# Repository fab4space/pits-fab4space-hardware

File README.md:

# pits-fab4space-hardware
pits-fab4space-hardware

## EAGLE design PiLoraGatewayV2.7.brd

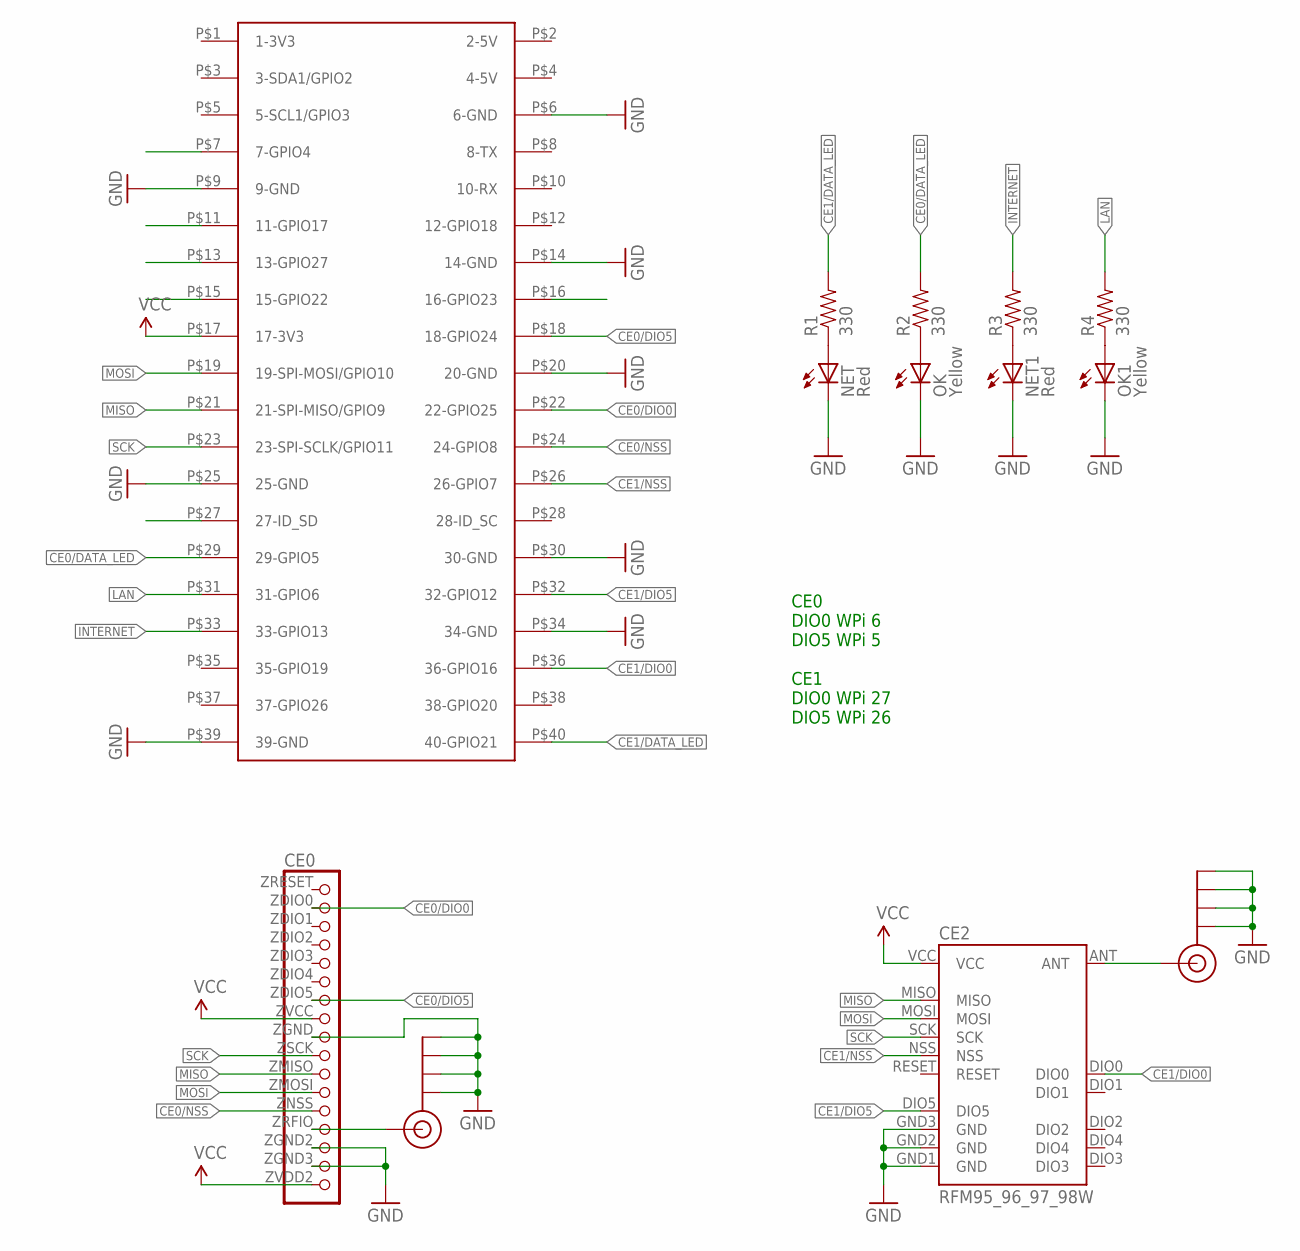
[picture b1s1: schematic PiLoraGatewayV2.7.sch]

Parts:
CE0: DRF1278F_BKOUTDP1276; ANYLINK_DP1276
CE2: RFM95_96_97_98W
J$1, J$2: SMA_EDGE; SMA-EDGE
NET, NET1: Red; LED-0603
OK, OK1: Yellow; LED-0603
R1, R2, R3, R4: 330; 0603-RES
U$1: RASPBERRY-PI+; RASPBERRY-PI-PLUS-CAM_NOTCH

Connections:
CE0/DATA_LED: R2.2, U$1.P$29 (29-GPIO5)
CE0/DIO0: CE0.ZDIO0 (DIO0), U$1.P$22 (22-GPIO25)
CE0/DIO5: CE0.ZDIO5 (DIO5), U$1.P$18 (18-GPIO24)
CE0/NSS: CE0.ZNSS (NSS), U$1.P$24 (24-GPIO8)
CE1/DATA_LED: R1.2, U$1.P$40 (40-GPIO21)
CE1/DIO0: CE2.DIO0, U$1.P$36 (36-GPIO16)
CE1/DIO5: CE2.DIO5, U$1.P$32 (32-GPIO12)
CE1/NSS: CE2.NSS, U$1.P$26 (26-GPIO7)
GND: CE0.ZGND (GND), CE0.ZGND2 (RGND1), CE0.ZGND3 (RGND2), CE2.GND1 (GND), CE2.GND2 (GND), CE2.GND3 (GND), J$1.GND@0 (GND), J$1.GND@1 (GND), J$1.GND@2 (GND), J$1.GND@3 (GND), J$2.GND@0 (GND), J$2.GND@1 (GND), J$2.GND@2 (GND), J$2.GND@3 (GND), NET.C, NET1.C, OK.C, OK1.C, U$1.P$6 (6-GND), U$1.P$9 (9-GND), U$1.P$14 (14-GND), U$1.P$20 (20-GND), U$1.P$25 (25-GND), U$1.P$30 (30-GND), U$1.P$34 (34-GND), U$1.P$39 (39-GND)
INTERNET: R3.2, U$1.P$33 (33-GPIO13)
LAN: R4.2, U$1.P$31 (31-GPIO6)
MISO: CE0.ZMISO (MISO), CE2.MISO, U$1.P$21 (21-SPI-MISO/GPIO9)
MOSI: CE0.ZMOSI (MOSI), CE2.MOSI, U$1.P$19 (19-SPI-MOSI/GPIO10)
unnamed: CE0.ZRFIO (RFIO), J$1.SIG (SIGNAL)
unnamed: NET1.A, R3.1
unnamed: OK1.A, R4.1
unnamed: OK.A, R2.1
unnamed: NET.A, R1.1
S$1: CE2.ANT, J$2.SIG (SIGNAL)
SCK: CE0.ZSCK (SCK), CE2.SCK, U$1.P$23 (23-SPI-SCLK/GPIO11)
VCC: CE0.ZVCC (VCC), CE0.ZVDD2 (VCC2), CE2.VCC, U$1.P$17 (17-3V3)

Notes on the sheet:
CE0 DIO0 WPi 6 DIO5 WPi 5 CE1 DIO0 WPi 27 DIO5 WPi 26

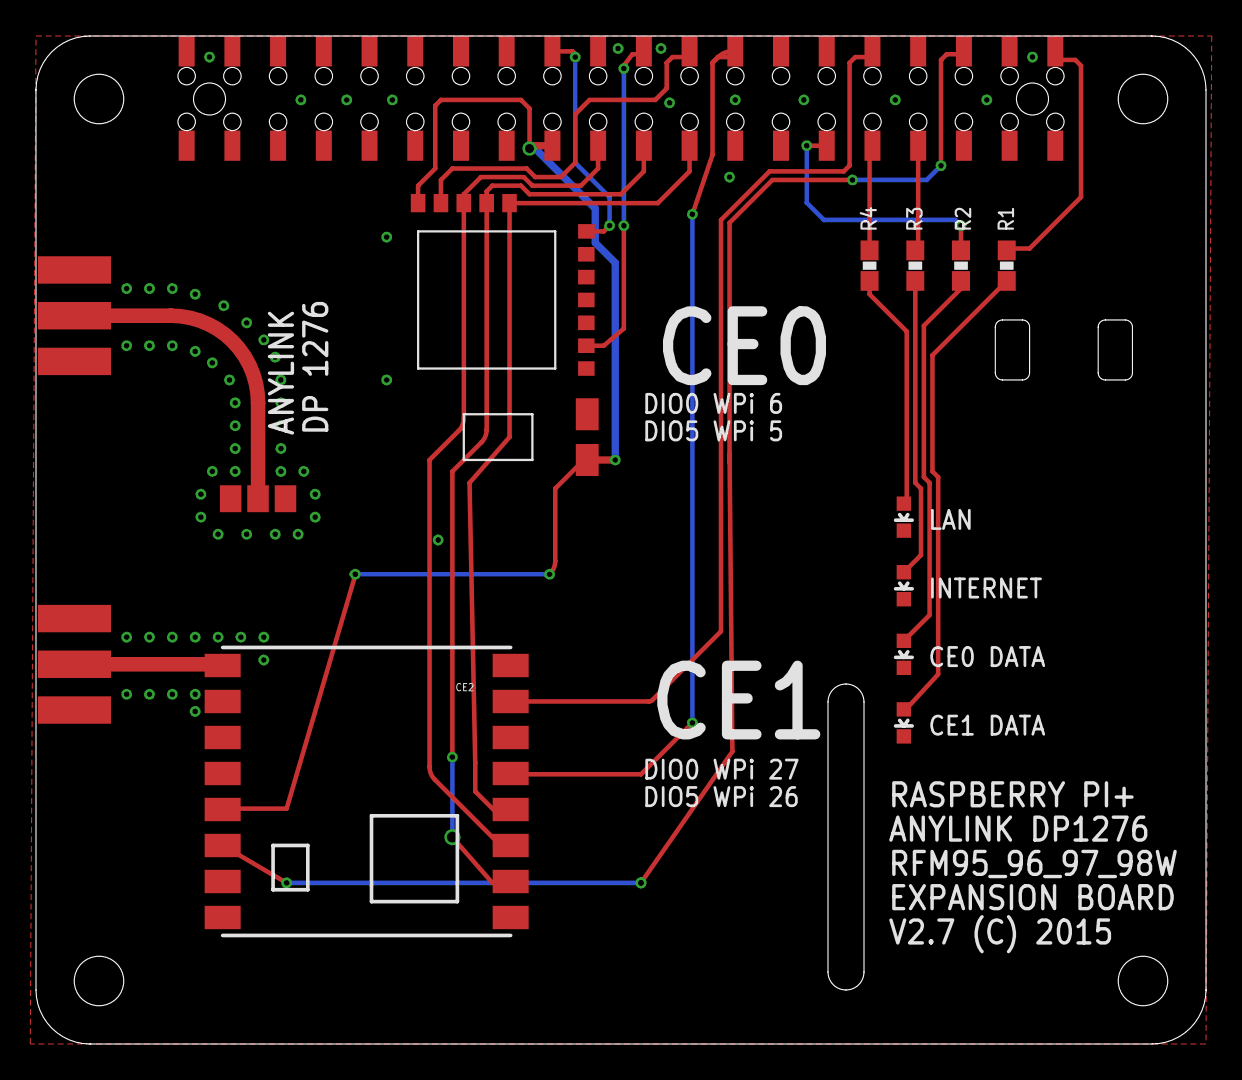
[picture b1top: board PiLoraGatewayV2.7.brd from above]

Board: 2 copper layers, 65.0 x 56.0 mm, 13 parts (0 on the bottom side), 21 nets.

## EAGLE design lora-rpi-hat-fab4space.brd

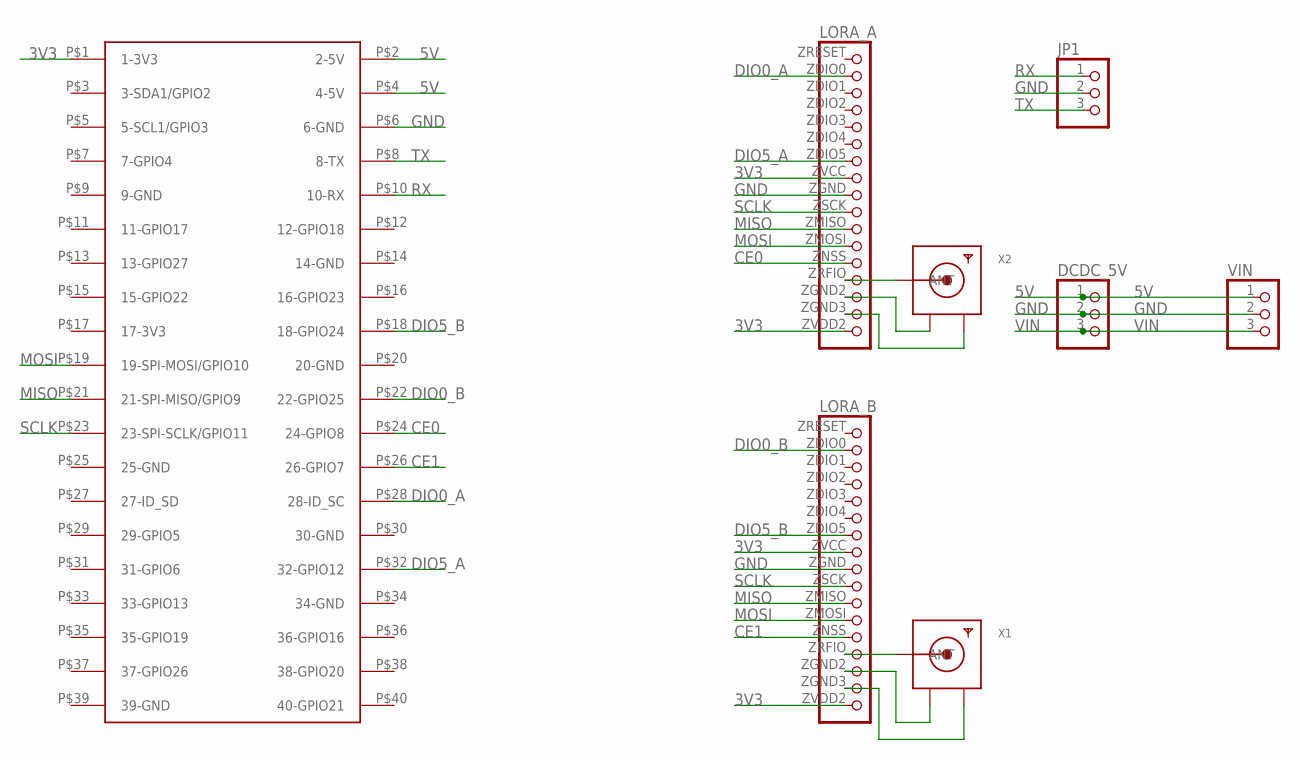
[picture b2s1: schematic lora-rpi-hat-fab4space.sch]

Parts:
DCDC_5V: PINHD-1X3; 1X03
JP1: PINHD-1X3; 1X03
LORA_A: DRF1278F_BKOUTDP1276; ANYLINK_DP1276
LORA_B: DRF1278F_BKOUTDP1276; ANYLINK_DP1276
U$1: RASPBERRY-PI+; RASPBERRY-PI-PLUS-CAM_NOTCH
VIN: PINHD-1X3; 1X03
X1, X2: SMACONNECTOR_EDGE; SMA_EDGELAUNCH

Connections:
3V3: LORA_A.ZVCC (VCC), LORA_A.ZVDD2 (VCC2), LORA_B.ZVCC (VCC), LORA_B.ZVDD2 (VCC2), U$1.P$1 (1-3V3)
5V: DCDC_5V.1, U$1.P$2 (2-5V), U$1.P$4 (4-5V), VIN.1
CE0: LORA_A.ZNSS (NSS), U$1.P$24 (24-GPIO8)
CE1: LORA_B.ZNSS (NSS), U$1.P$26 (26-GPIO7)
DIO0_A: LORA_A.ZDIO0 (DIO0), U$1.P$28 (28-ID_SC)
DIO0_B: LORA_B.ZDIO0 (DIO0), U$1.P$22 (22-GPIO25)
DIO5_A: LORA_A.ZDIO5 (DIO5), U$1.P$32 (32-GPIO12)
DIO5_B: LORA_B.ZDIO5 (DIO5), U$1.P$18 (18-GPIO24)
GND: DCDC_5V.2, JP1.2, LORA_A.ZGND (GND), LORA_B.ZGND (GND), U$1.P$6 (6-GND), VIN.2
MISO: LORA_A.ZMISO (MISO), LORA_B.ZMISO (MISO), U$1.P$21 (21-SPI-MISO/GPIO9)
MOSI: LORA_A.ZMOSI (MOSI), LORA_B.ZMOSI (MOSI), U$1.P$19 (19-SPI-MOSI/GPIO10)
unnamed: LORA_A.ZRFIO (RFIO), X2.P (ANT)
unnamed: LORA_A.ZGND2 (RGND1), X2.GND@2 (GND3)
unnamed: LORA_A.ZGND3 (RGND2), X2.GND@1 (GND4)
unnamed: LORA_B.ZRFIO (RFIO), X1.P (ANT)
unnamed: LORA_B.ZGND2 (RGND1), X1.GND@2 (GND3)
unnamed: LORA_B.ZGND3 (RGND2), X1.GND@1 (GND4)
RX: JP1.1, U$1.P$10 (10-RX)
SCLK: LORA_A.ZSCK (SCK), LORA_B.ZSCK (SCK), U$1.P$23 (23-SPI-SCLK/GPIO11)
TX: JP1.3, U$1.P$8 (8-TX)
VIN: DCDC_5V.3, VIN.3

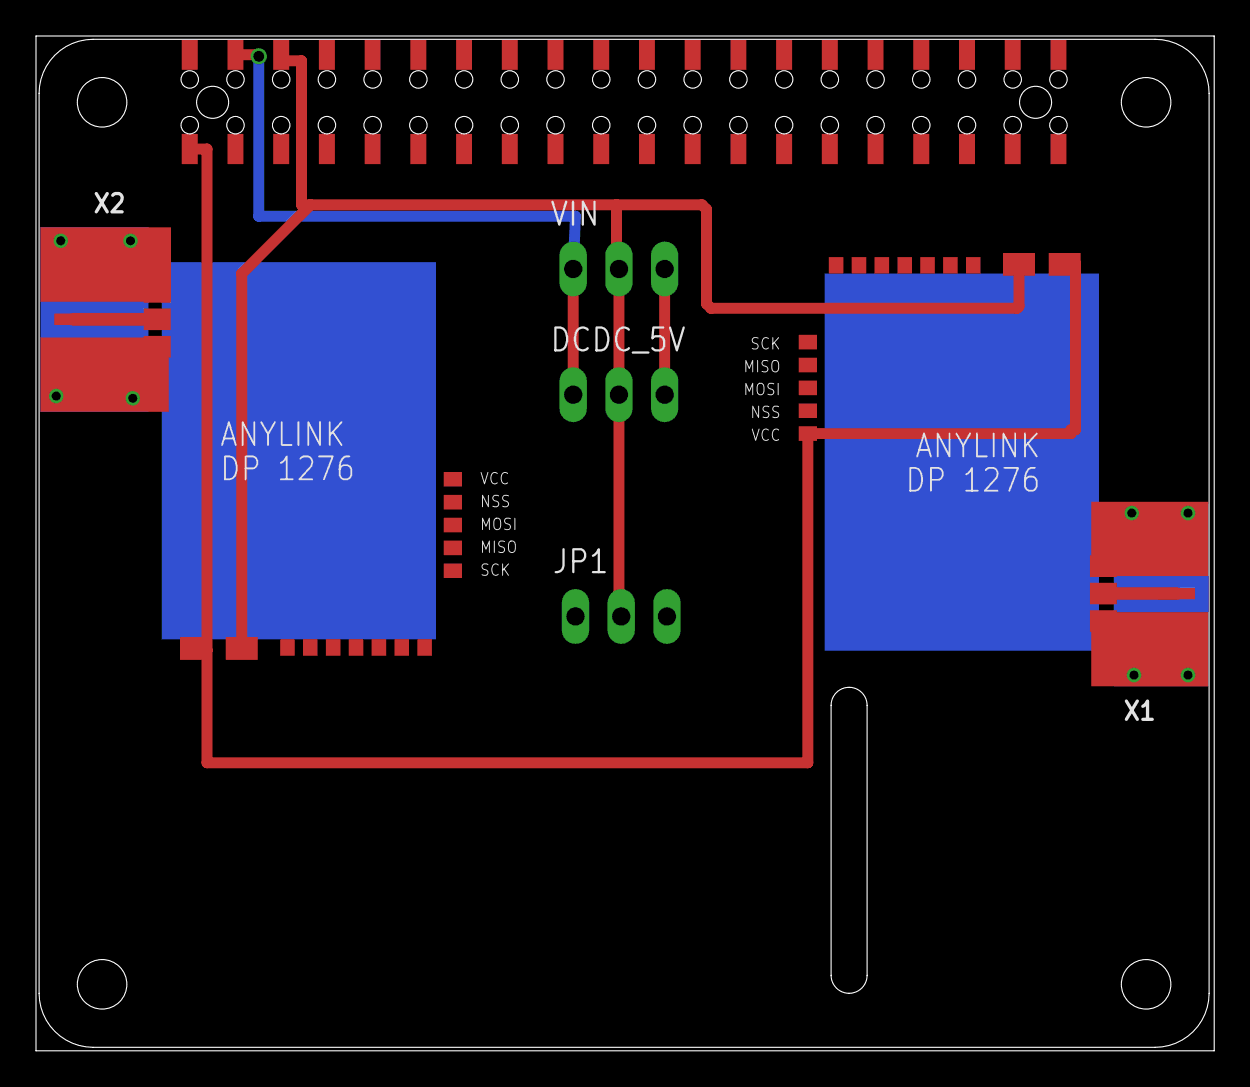
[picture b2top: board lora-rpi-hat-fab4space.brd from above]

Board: 2 copper layers, 65.5 x 56.4 mm, 8 parts (0 on the bottom side), 21 nets.

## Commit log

2015-10-29 Added lora-rpi-hat-fab4space
2015-10-29 Added adafruit library including DP1276 module and sma connectors.
2015-11-04 Updated files from Anthony.
2015-11-04 removed old files
2015-11-04 Added gerber file.
2015-11-18 Added new version with dual lora modules: Anylink DP1276 and RFM9xW.

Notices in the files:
PiLoraGatewayV2.7.brd:
V2.7 (C) 2015
parts and their libraries:
SparkFun: Licensing: CC v3.0 Share-Alike You are welcome to use this library for commercial purposes.
